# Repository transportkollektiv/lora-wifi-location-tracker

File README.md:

# LoRa Wifi Location Tracker

This is a ESP8266 and RFM96 based for low power geolocation tracker. It uses wifi networks for location discovery instead of GPS. Accuracy is not as good as GPS and locations can only be calculated if there is any nearby wifi networks. For location calculation a wifi geolocate service like [mozilla](https://location.services.mozilla.com/) or [google](https://developers.google.com/maps/documentation/geolocation/intro) is needed.
The location is not calculated on the device. The small data for calculating the location is send out via LoRaWAN and can then calculated on server. You can use [cycle-ttn-wifi](https://github.com/transportkollektiv/cykel-ttn-wifi) as location calculation bridge.

## Hardware

You can find .brd and .sch files (created in eagle) and the ready to use gerber files for the *lortinchen*-PCB in the `hardware` folder. More info in [`README.md`](./hardware/README.md) in the hardware folder.
The board can be power by two AA batteries.

## Firmware configuration

For LoRaWAN configuration rename `config.sample.h` to `config.h` and fill the file with your LoRaWAN device config. Development, configuration, building and flashing can all be done in [PlatformIO](https://platformio.org/).
To make the wifi scan more effective, we currently have to patch `ESP8266WiFiScan`. Call `make patch` to modify the file in your platformio framework-arduinoespressif8266 - or look into the `ESP8266WiFiScan.patch` if you want to make the changes yourself.
More on physically flashing firmware at `hardware/README.md`.

## TTN decoder script

The [TTN](https://www.thethingsnetwork.org/) payload decoder script can be found in [`ttn-decoder-script.js`](./ttn-decoder-script.js) for TTN Stack V2 or in [`ttnv3-decoder-script.js`](./ttnv3-decoder-script.js) if you are using TTN Stack V3.

## Improve coverage

You can improve [coverage of mozillas location service](https://location.services.mozilla.com/map) using the [mozilla stumbler app](https://play.google.com/store/apps/details?id=org.mozilla.mozstumbler) for android or by [activating location data collection in firefox for android](https://support.mozilla.org/en-US/kb/improve-mozilla-location-services-turning-location).

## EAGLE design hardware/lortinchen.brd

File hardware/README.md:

# Lortinchen

Lortinchen is a small PCB combining an ESP8266 with an RFM96 for Lora Communication. We use this as a Wifi location tracker in our OpenBike project to track our Bikes.

## Flash firmware

To flash firmware before soldering the ESP on the PCB, you can use an *ESP-12 test board fixture programmer*. So you don't need to solder a connection to a Serial-USB-Adapter and don't need the flash and reset buttons.

If you want to update or flash firmware after soldering, you need the 1K resistors and the flash and reset  buttons. Then solder GND, RX, TX and 3V to your Serial-USB-Connector. To go into flash-mode hold flash button, press reset, then release flash button. Now you can flash the firmware from PlatformIO.

## Parts

### Required

 * ESP8266 Modules (ESP-12E or ESP-12F with on board PCB antenna or ESP-07 or ESP-07S for external antennas)
 * RFM96
 * 5x 10K 0603 resistors
 * 1x 100uF (107C/6032) capacitor

### Optional

 * 2x 1K 0603 resistors (for serial connection and flashing after soldering)
 * 2x SMD 2Pin 3X4 mm tactile buttons (for easy flashing and resetting after soldering)
 * 1x AMS111733 LDO (only if power supply is more than 3,3V, but will consume more power.)
 * 1x 680K and 1x 100K 0603 resistor (for voltage devider), now supported in the firmware to mesure voltage. If you don't use the AMS111733, connect the 12V and the 3V Pin to mesure voltage.

## Power supply

The Board can be powered by two AA (LR6) batteries on the 3V3 pad, without the AMS111733 installed. Our first test-devices are running now for around 4 months without changing batteries.

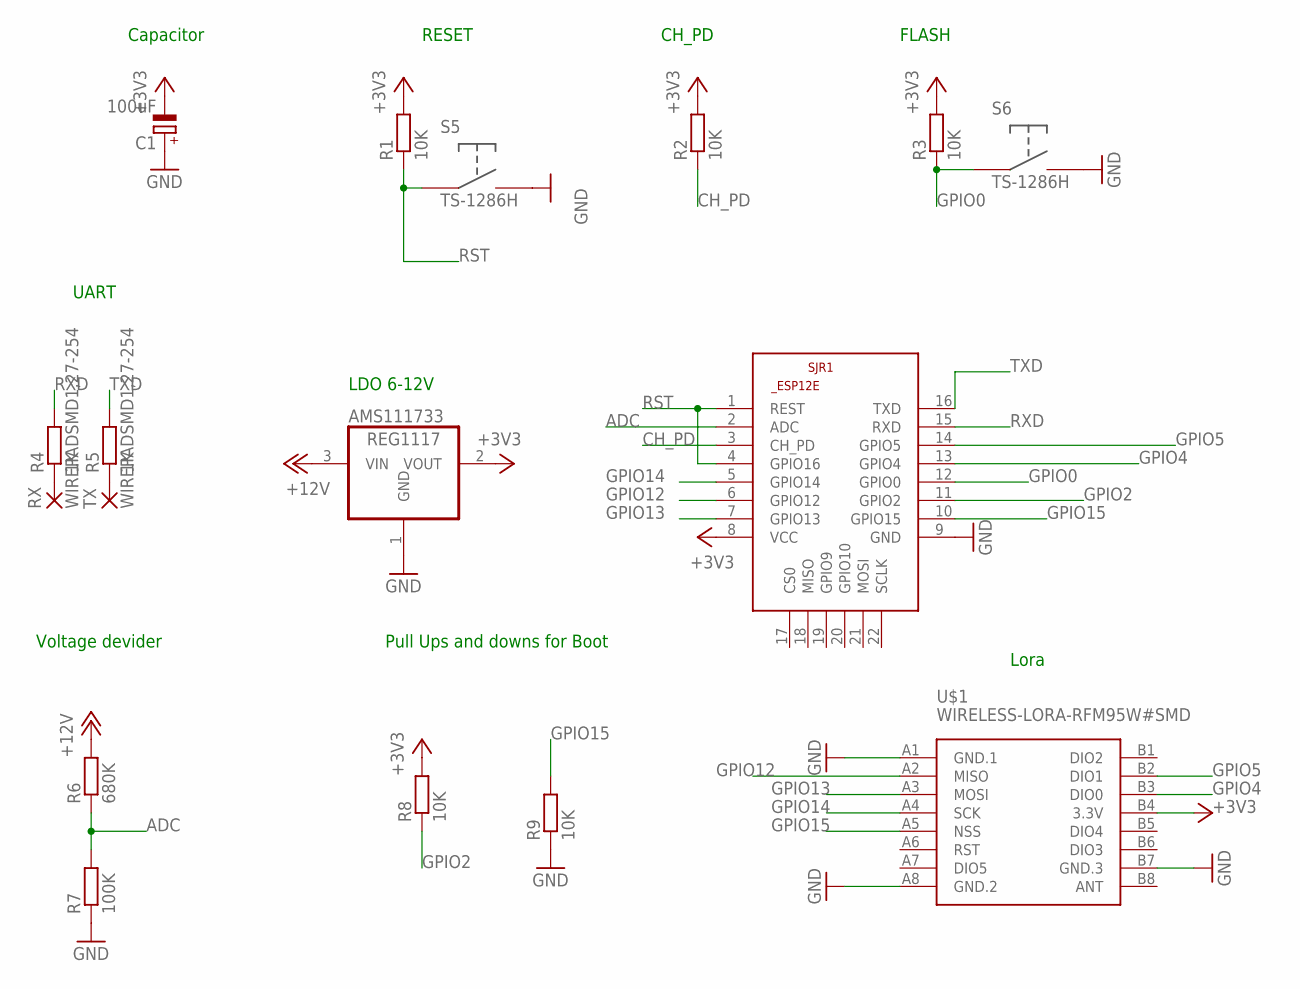
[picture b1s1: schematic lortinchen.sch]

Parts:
AMS111733: REG1117; SOT223
C1: 100uF; C/6032-28R
R1, R2, R3, R8, R9: 10K; R0603
R4, R5: 1K; R0603
R6: 680K; R0603
R7: 100K; R0603
RX: WIREPADSMD1,27-254; SMD1,27-2,54
S5, S6: TS-1286H; TS-1268H
SJR1: ESP8266-12EESP12E; ESP8266-ESP12E
TX: WIREPADSMD1,27-254; SMD1,27-2,54
U$1: WIRELESS-LORA-RFM95W#SMD

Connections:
+3V3: AMS111733.2 (VOUT), C1.-, R1.2, R2.2, R3.2, R8.2, SJR1.8 (VCC), U$1.B4 (3.3V)
+12V: AMS111733.3 (VIN), R6.2
ADC: R6.1, R7.2, SJR1.2 (ADC)
CH_PD: R2.1, SJR1.3 (CH_PD)
GND: AMS111733.1 (GND), C1.+, R7.1, R9.1, S5.P$2, S6.P$2, SJR1.9 (GND), U$1.A1 (GND.1), U$1.A8 (GND.2), U$1.B7 (GND.3)
GPIO0: R3.1, S6.P$1, SJR1.12 (GPIO0)
GPIO2: R8.1, SJR1.11 (GPIO2)
GPIO4: SJR1.13 (GPIO4), U$1.B3 (DIO0)
GPIO5: SJR1.14 (GPIO5), U$1.B2 (DIO1)
GPIO12: SJR1.6 (GPIO12), U$1.A2 (MISO)
GPIO13: SJR1.7 (GPIO13), U$1.A3 (MOSI)
GPIO14: SJR1.5 (GPIO14), U$1.A4 (SCK)
GPIO15: R9.2, SJR1.10 (GPIO15), U$1.A5 (NSS)
unnamed: R4.1, RX.1
unnamed: R5.1, TX.1
RST: R1.1, S5.P$1, SJR1.1 (REST), SJR1.4 (GPIO16)
RXD: R4.2, SJR1.15 (RXD)
TXD: R5.2, SJR1.16 (TXD)

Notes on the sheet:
RESET
CH_PD
FLASH
LDO 6-12V
Capacitor
UART
Voltage devider
Pull Ups and downs for Boot
Lora

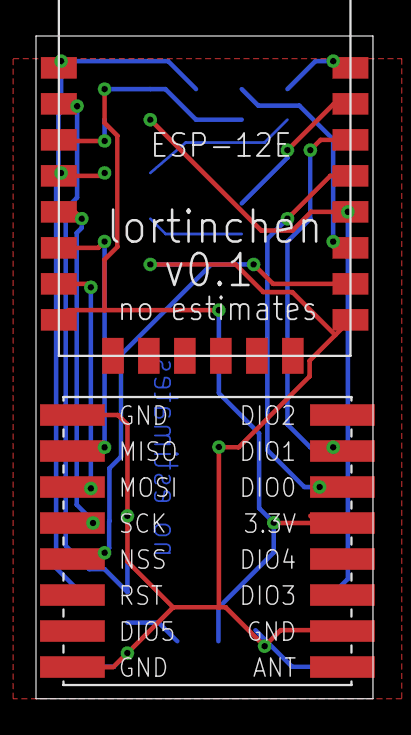
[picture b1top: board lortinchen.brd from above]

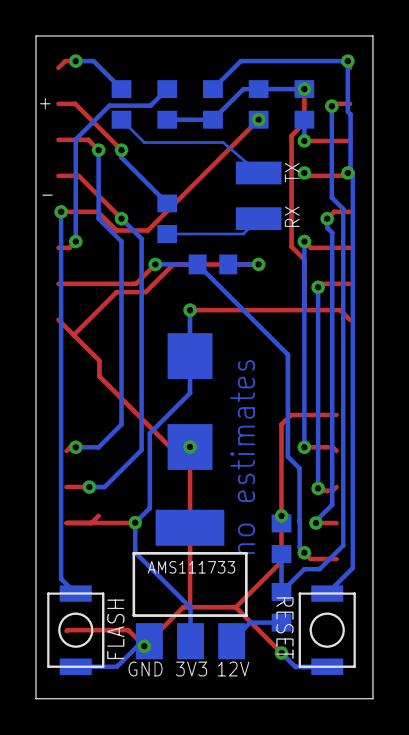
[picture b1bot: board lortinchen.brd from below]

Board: 2 copper layers, 18.7 x 36.8 mm, 17 parts (15 on the bottom side), 18 nets.

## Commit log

2020-01-15 first but still to late commit
2020-01-15 added config sample
2020-01-15 added hardware
2020-01-15 updated README with flashing info
2020-01-15 basic readme for hardware
2020-01-15 readme flash firmware
2020-01-15 typos
2020-01-15 added image of lortinchen
2020-01-15 fixed links
2020-01-15 added ttn payload decoder script
2020-01-15 added notes to power supply and power consumption
2020-07-23 shut down wifi after scan, saves energy
2020-07-23 decoder script with payload versions and voltage
2020-07-23 Payload version and Battery voltage
2020-07-28 decoder script: fixed null voltage values, toFixed
2020-08-12 Update README.md
    added footprint for 100uF capacitor
2020-09-09 added hw requirements for new firmware
2020-09-16 write dev addr to serial output
2021-02-26 switched to MCCI LMIC Lorawan libary
2021-02-27 otaa with keys in RTC RAM (WIP)
2021-04-23 add decoder script for ttn v3
2021-07-08 move config above lmic, use standard types
2021-07-08 move CFG_eu868 lmic flag into config
2021-07-08 let lmic really really use our config, not the default values
2021-07-08 add makefile for building
2021-07-08 add patch for esp8266wifiscan to improve scanning
2021-07-08 create github action for test builds
2021-09-10 pio building is weird, but it seems now its compiling with the right config
2021-09-10 feat: otaa with keys in RTC RAM
2021-09-10 fix: SLEEP_DURATION has to be static
2021-09-10 reproducible builds: use last git commit timestamp as SOURCE_DATE_EPOCH
2021-11-04 chore: repo moved from stadtulm to transportkollektiv

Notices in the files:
parts and their libraries:
diy-modules: Released under the Creative Commons Attribution 4.0 International License: http://creativecommons.org/licenses/by/4.0
